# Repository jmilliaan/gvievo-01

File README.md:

# gvievo-01 — AGV / AMR platform

Control software for a 150 kg differential-drive vehicle. Two Oriental Motor
BLV-R drivers in CiA 402 Profile Velocity mode share one `can0` with a SICK MLS
magnetic line sensor (track reading and IMU); a SICK nanoScan3 safety scanner,
a Chafon RFID reader and a Modbus I/O island sit on Ethernet. The vehicle runs
as one systemd unit, `amr.service`: a supervisor, the hardware nodes, a web UI
on port 5001, and one *mode layer* at a time.

> ### gvievo-ce branch (2026-11-23)
> This branch is gvievo-main adapted to the **kyb unit** (host `gvipc-ce`, previously on
> `kyb-trackless`). It is the **tape product, like gvievo-main** (`tracked: null`): MLSE line
> following, slam_toolbox/AMCL, tape localization in shadow (`live: false`) until this site is
> taught. No MQTT: station calling stays off. Hardware: DIO island on enp1s0
> (`192.168.1.40`), nanoScan3 on enp2s0 (host `192.168.3.1`), enp3s0 empty. No Manual Arm input:
> MANUAL is always armed unless an emergency (E-stop OK = DI08 from Q3). Outputs DO0 movement horn,
> DO1 alarm horn only. See `documentation/electrical/01-schematic/io-mapping.md` section 4.

> ### Status (2026-09-21)
> **Two products on one stack.** The vehicle is a magnetic-tape AGV (the
> `LINE` mode: `amr_line`, ported from the tape controller that drove it
> before) with the SLAM AMR (`MAPPING`/`NAVIGATION`: slam_toolbox, AMCL, Nav2)
> as the upgrade. Which one a vehicle is comes from its profile.
>
> **The legacy standalone controller is gone (U11).** `main.py`, `app/` and
> `canworker.py` were deleted on 2026-09-21 after the ported LINE mode was
> accepted on the vehicle; the last deployable revision is tagged
> `legacy-final`. Its offline run logs are archived under
> `manuals/obsolete/legacy-runs/`. Nothing else on the vehicle owns `can0`.
>
> **The nanoScan3 is owned by the ROS stack** (`sick_safetyscanners2`); its
> liveness is read from `/amr/localization_state`. The protective-field
> outputs reach the drives through the FX3 in hardware, and the software only
> *reads* them (`/output_paths`) to explain a stop.

| | |
|---|---|
| Runtime | `amr.service` → `deploy/amr-supervisor.sh` → ROS 2 Humble, `amr_ws/` |
| Bus | CANopen 125 kbps, 50 Hz feedback by TPDO, setpoint by RPDO |
| Nodes | 1 left driver, 2 right driver, 10 SICK MLS (track at 100 Hz + gyro) |
| Manual | pendant and web jog 0.314 m/s = 1000 motor r/min (gvievo-ce 2026-11-23; was 0.60), only under selector MANUAL |
| Auto | tracked NORMAL 0.50 m/s (trips: mission `cruise_mps` 0.40), HIGH 0.90 m/s (`auto_high_ratio` 1.79, 2850 r/min motor; agv-01 since 2026-11-17, agv-02 still 1.7 / 0.85) only inside an MLS marker zone or a HIGH area; trips also NORMAL+ 0.65 m/s (`auto_plus_ratio` 1.3) inside a NORMAL+ area (slower area wins where they overlap); trackless 0.60 m/s |
| Tests | `tests/run_all.py` (`EXPECTED_CHECKS` guards the count) + `pytest` per ROS package, no hardware |

---

## ⚠️ Safety model

**This software moves a 150 kg vehicle and has no authentication.** Anyone who
can reach port 5001 can drive it. Keep it on a trusted network.

**The panel owns every entry into motion.** Manual jog (browser or pendant)
works only while the selector rests in MANUAL and the supervisor has granted
the manual lease; every autonomous start — a route, a survey move, the tape
follower — needs the selector in AUTO *and* a fresh physical Start press. No
web page can start the vehicle.

**One exception, only with `station.enabled: true` (default false).** An order
accepted from the station PC over MQTT leaves HOME for ATT with no Start press:
once, in AUTO, through the same 2 s horn, with no trolley detected and the rear
field clear. Every other stop and every hold still waits for Start. The bridge
holds no lease and no command topic, and the link is plain MQTT with broker
passwords and an ACL. This is a subset of VDA5050 3.0.0, not compliant. See
`manuals/station-call-plan.md`.

**A manual direction is HELD, not latched.** The jog pad re-POSTs while a
button is down; the command mux drops a stream whose stamp is older than its
`valid_for_s` (0.2 s). A closed tab, a dropped Wi-Fi link and a released
button are indistinguishable to the vehicle, which is the point.

**Arming excites the motor; it does not free it.** CiA 402 "Operation enabled"
is a servo lock, not a free shaft. Only the drive's `FREE` input releases the
brake, and `FREE` is on the CAN write deny-list. A disarmed vehicle cannot be
pushed either.

**Nothing in this repo is in the safety path.** The chain is lidar/encoders →
FX3 → HWTO1/HWTO2 → STO, wired in hardware with EDM returned to the FX3. Nothing
read over CAN or Ethernet is rated, redundant or certified, and nothing here may
decide whether it is safe to move. What the software adds is *recovery*: after
a lidar stop it resumes by itself once the field is clear; after the E-stop
button it waits for Start.

---

## Running

```bash
sudo systemctl start amr.service          # the only AGV boot service
systemctl status amr.service --no-pager
journalctl -u amr.service -f
```

Everything operational — boot checks, mode swaps, surveys, routes, holds,
rollback — is in [amr_ws/RUNBOOK.md](amr_ws/RUNBOOK.md). Deployment files
(`amr.service`, `amr.env`, the launch wrappers, `install.sh`, `validate.sh`, the
CAN bridge unit and udev template, the unclean-death helpers, the watchdog drop-ins)
are under [amr_ws/deploy/](amr_ws/deploy/); the platform freeze (ROS snapshot
source, apt pins and holds, `freeze.sh`) is under
[amr_ws/deploy/platform/](amr_ws/deploy/platform/). RUNBOOK section 5 says what
each installs.

**Which vehicle** comes from `AGV_PROFILE`, naming a file in `profiles/`.
Unset means `agv-01`. A name with no matching file is fatal at boot.

Bench work with the service stopped:

```bash
python3 -m agv_core.drivers.canbus.verify_bus       # nodes 1, 2, 10 answer
python3 -m agv_core.drivers.canbus.verify_drivers   # BLV-R identity and state
python3 -m agv_core.drivers.canbus.read_mls stream --nmt   # the track reading
python3 -m agv_core.drivers.canbus.read_imu show
```

Every bench tool takes the CAN owner lock first and refuses, naming the owner,
while `amr.service` (or another tool) holds it.

### Dependencies

ROS 2 Humble with Nav2, slam_toolbox, robot_localization,
`sick_safetyscanners2`; `python-can`, `pymodbus`, `flask`. The vehicle image
has them; nothing is pinned in `pyproject.toml` so the offline suite runs on a
dev box without them.

---

## Layout

**`agv_core/` is the library, `amr_ws/` is the runtime.** The runtime imports
the library; the library imports neither ROS nor Flask.

```
agv_core/          The vehicle library. No ROS, no Flask, no web tier.
  config.py          Loads and validates the profile. Everything imports this.
  kinematics.py      Wheel <-> body conversions from the profile geometry.
  ownerlock.py       The can/dio owner locks (fcntl); one owner per device.
  alarms.py, mission.py, paths.py, se2.py, fsio.py, fsutil.py, disk.py,
  panel.py, canmon.py, events.py, blindrun.py, lidarframe.py
  drivers/           dio.py (Modbus I/O island), rfid.py (Chafon reader)
  drivers/canbus/    CANopen decoders, the write deny-list (guard.py), RPDO
                     setup, and the bench tools listed above.

amr_ws/            The ROS 2 workspace (colcon, symlink install).
  src/amr_base         drive_node (the can0 owner), panel_node, cmd_mux,
                       odometry, commissioning, the MLS track reader
  src/amr_bringup      the supervisor, launch files, deploy/ and env/
  src/amr_line         LINE mode: the tape engine (autopilot.py, branch.py are
                       the verbatim port), the follower node, its authority
  src/amr_mission      routes, the run FSM, survey moves, the executor
  src/amr_navigation   route compiler, validation, Nav2 parameters
  src/amr_localization SLAM/AMCL glue, readiness, the localisation monitor
  src/amr_maps         map bundles and revisions
  src/amr_web          the Flask UI on 5001 and its ROS adapter
  src/amr_station      station_bridge_node: MQTT to the station PC (station.enabled only)
  src/amr_sim          fake base/panel/IMU/trolley, synthetic scan and tape
  src/amr_interfaces   messages and services

tests/             offline checks for agv_core (count: EXPECTED_CHECKS). run_all.py runs them.
profiles/          One JSON per vehicle. Every tunable parameter lives here.
manuals/           Device documentation, current plans and runbooks; obsolete/ = history
                   (vehicle reports, the SLAM plan, finished or superseded plans).
pyproject.toml     Packages agv_core; also the shared ruff and pytest config.
```

**`agv_core` is a real package, imported by package path.** `from agv_core
import config`, `from agv_core.drivers.canbus import guard`. ROS nodes run out
of the colcon install space, which is outside the repo, so
`env/vehicle.sh` (sourced by the service's `amr-supervisor.sh`) and `env/sim.sh`
put the repo root on `PYTHONPATH`; `amr_ws/deploy/validate.sh` refuses to install
if `agv_core/` is not where they expect it.

**Dependency graph:** `agv_core.config` imports only the standard library;
everything else imports it. No cycles. Nothing in `agv_core/drivers/canbus/`
imports `config` — those modules stay runnable on a bench. `tests/test_layout.py`
pins the package boundary.

---

## How it works

### One owner per device

`amr_base.drive_node` is the only process that opens `can0`, `panel_node` the
only one that writes the I/O island; each takes its owner lock at start. Inside
`drive_node`, one bus thread does every CAN transaction: feedback arrives by
TPDO at 50 Hz, the setpoint leaves by RPDO, and the MLS track reading rides on
TPDO1 `0x18A` at 100 Hz. Everything above it — mux, executor, follower — sends
stamped commands on topics and holds a *permit*; nothing else touches the bus.

### Authority

The supervisor grants one **lease** at a time (manual, autonomous, commissioning
or line), the command mux applies only the source that lease allows, and the
physical panel gates every transition: MANUAL for jog, AUTO plus a Start edge
for anything autonomous, Reset to end a run. A lease is bound to a
*generation* that rotates on every mode swap, so a replaced layer's commands
can never look fresh to the new mux.

### What the vehicle may write over CAN

[agv_core/drivers/canbus/guard.py](agv_core/drivers/canbus/guard.py) enforces a
deny-list on every write path of the bus owner (`amr_base.canopen`):

| | |
|---|---|
| **permitted** | `6040h` controlword, `6060h` modes, `6083h`/`6084h` ramps, `60FFh` target velocity, `607Ah`/`6081h` for PP, `1017h` heartbeat, PDO communication parameters |
| **refused** | `403Eh` (bit 6 is **FREE** — releases the holding brake on *both* drive wheels), `40D0h` clear ETO, `40C0h` alarm reset, `6040h` bit 7 fault reset, `1010h`/`1011h` store/restore, all `4xxxh` parameters, the PP safety objects |

A denied write raises rather than being silently dropped. RPDO mappings are
admitted only if the mapped object is itself writable — a mapping is a write
path by another name. Clearing ETO or resetting an alarm automatically would
be an automatic restart, which ISO 3691-4 prohibits: a latched drive alarm is
cleared by a power cycle, not by software.

### The MLS

The line sensor serves both products: its **track reading** (LCP positions,
`#LCP`, marker) feeds the tape follower, and its **gyro** carries the heading
for SLAM (the EKF weights it far above the wheels). Tape to the vehicle's left
reads *positive* millimetres. The reader starts the node by NMT so TPDO1 flows
and falls back to SDO polling (monitor only, ~10 Hz) if it does not; the
follower refuses to run on SDO samples or below `line_min_track_hz`.

---

## Configuration

Everything tunable lives in `profiles/<name>.json`, selected by `AGV_PROFILE`.
**`agv_core/config.py`'s docstring is the manual.**

1. **Unknown and missing keys are both fatal.**
2. **Only primitives are stored.** Anything derivable is derived.
3. **Validation runs before anything is published.**
4. **`profile_name` must match the filename.**

Speeds, ramps, the jog and pendant limits, the PP lock and the tape engine's
gains (`autopilot`) are all there — and the product: top-level
`"tracked": false` is the SLAM AMR, `true` the tape AGV that boots into LINE
and refuses maps and routes, `null` both: boots into LINE, surveys and the AMCL
position on the Mapping page (RUNBOOK §1, §2). The web UI's Params page shows every
value the running nodes actually use beside the profile's.

---

## Testing

```bash
python3 tests/run_all.py                                   # no hardware
cd amr_ws && source install/setup.bash && source env/vehicle.sh
env AMR_SIM_TESTS=0 ROS_DOMAIN_ID=89 python3 -m pytest -q src/*/test   # per package
ruff check agv_core tests && (cd amr_ws && ruff check src)
```

`run_all.py` **pins both the module list and the total check count**; a module
that stops being imported fails the run instead of silently costing coverage.
Raise `EXPECTED_CHECKS` deliberately, with a note, when adding checks; never
lower it to get a green run.

Simulation launch tests are opt-in (`AMR_SIM_TESTS=1`) and check mechanisms,
not tolerances. Vehicle acceptance is a witnessed session from a
`VEHICLE-TEST-*.txt` file at the repo root; reports go to
`manuals/obsolete/vehicle-reports/`.

---

## Invariants

**`agv_core` may not import ROS or Flask.** The bench tools and the nodes both
import it. `tests/test_layout.py` scans for it, lazy imports included, and
also refuses a bare sibling import inside the package.

**`agv_core/drivers/canbus/` is a runtime dependency, not a scratch directory.**
`amr_base.canopen` imports from it. Do **not** make those modules import
`config`; where they need a vehicle-specific value, take it as a parameter
defaulting to the module constant.

**NMT is per node.** The drive link puts *the drives* in Pre-operational for
PDO setup and starts *the drives*; it never broadcasts. A broadcast silenced
the MLS on the vehicle (2026-09-21).

**Wheel sign convention:** both drivers take a **positive** `60FFh` to travel
forward. If you swap a motor, re-flash a driver or remount a wheel, re-verify
on blocks and set `vehicle.invert_left` / `invert_right`.

**`autopilot.py` and `branch.py` are the port.** They are the engine that drove
this vehicle on tape and are not edited; if the gains look wrong, the gains
move in the profile.

---

## Known gaps

- **Tracked jobs are sim-tested only** (2026-10-08): the mission is the site's RFID
  tag table (`missions/line-a.json`, schema in `agv_core/mission.py`) - Home, an
  always-stop, destination stops (MRU1-4) and a track-end U-turn; speed comes from the MLS
  marker pairs (`high_zone`), not RFID (2026-10-09).
  The job (mission + destination) is set on Run; the vehicle may start anywhere
  on the line, then the physical Start runs it. Tag ids `0010`... are assumed to be what the RFID
  panel shows; stop positions, the 2 s speed change, the tape-end overshoot and the
  pivot reacquisition angle are settled on the floor.
- **No floor run of the tape follower yet** (LINE acceptance section 4).
- **0.90 m/s (tracked HIGH, agv-01; 0.85 before 2026-11-17) runs with no software gate,
  unvalidated** (operator decision 2026-10-08, manuals/tracked-speed-plan-1-no-slam.md D2;
  raised to 2850 r/min by the owner 2026-11-17): the nanoScan3 field set
  (`lidar.zones_validated` false) and the STO stopping distance from 0.90 m/s
  are a floor check before the first HIGH run. There is no FX3 encoder speed monitoring
  yet. HIGH needs a mission `high_zone` (MLS outer/inner marker codes); `line-a` carries one
  (codes 2/1), so HIGH runs wherever those marker pairs are laid.
- **`6064h` scaling is unverified** beyond the commissioning runs.
- **Backlash is unmeasured.** The encoders are motor-side of a 30:1 gearhead.
- **RFID reader is still on the US region (902.75–927.25 MHz)** and every read so far reports channel 0;
  Indonesia permits 920–923 MHz. Protocol is captured and CRC-verified (2026-10-08). The 0x0050
  heartbeat ships off (`rfid.heartbeat_s` 0) until a bench run shows it does not disturb streaming.
- MEXE02 load inertia is still `0: Small (2×)`; should be `1: Medium (7.5×)`.

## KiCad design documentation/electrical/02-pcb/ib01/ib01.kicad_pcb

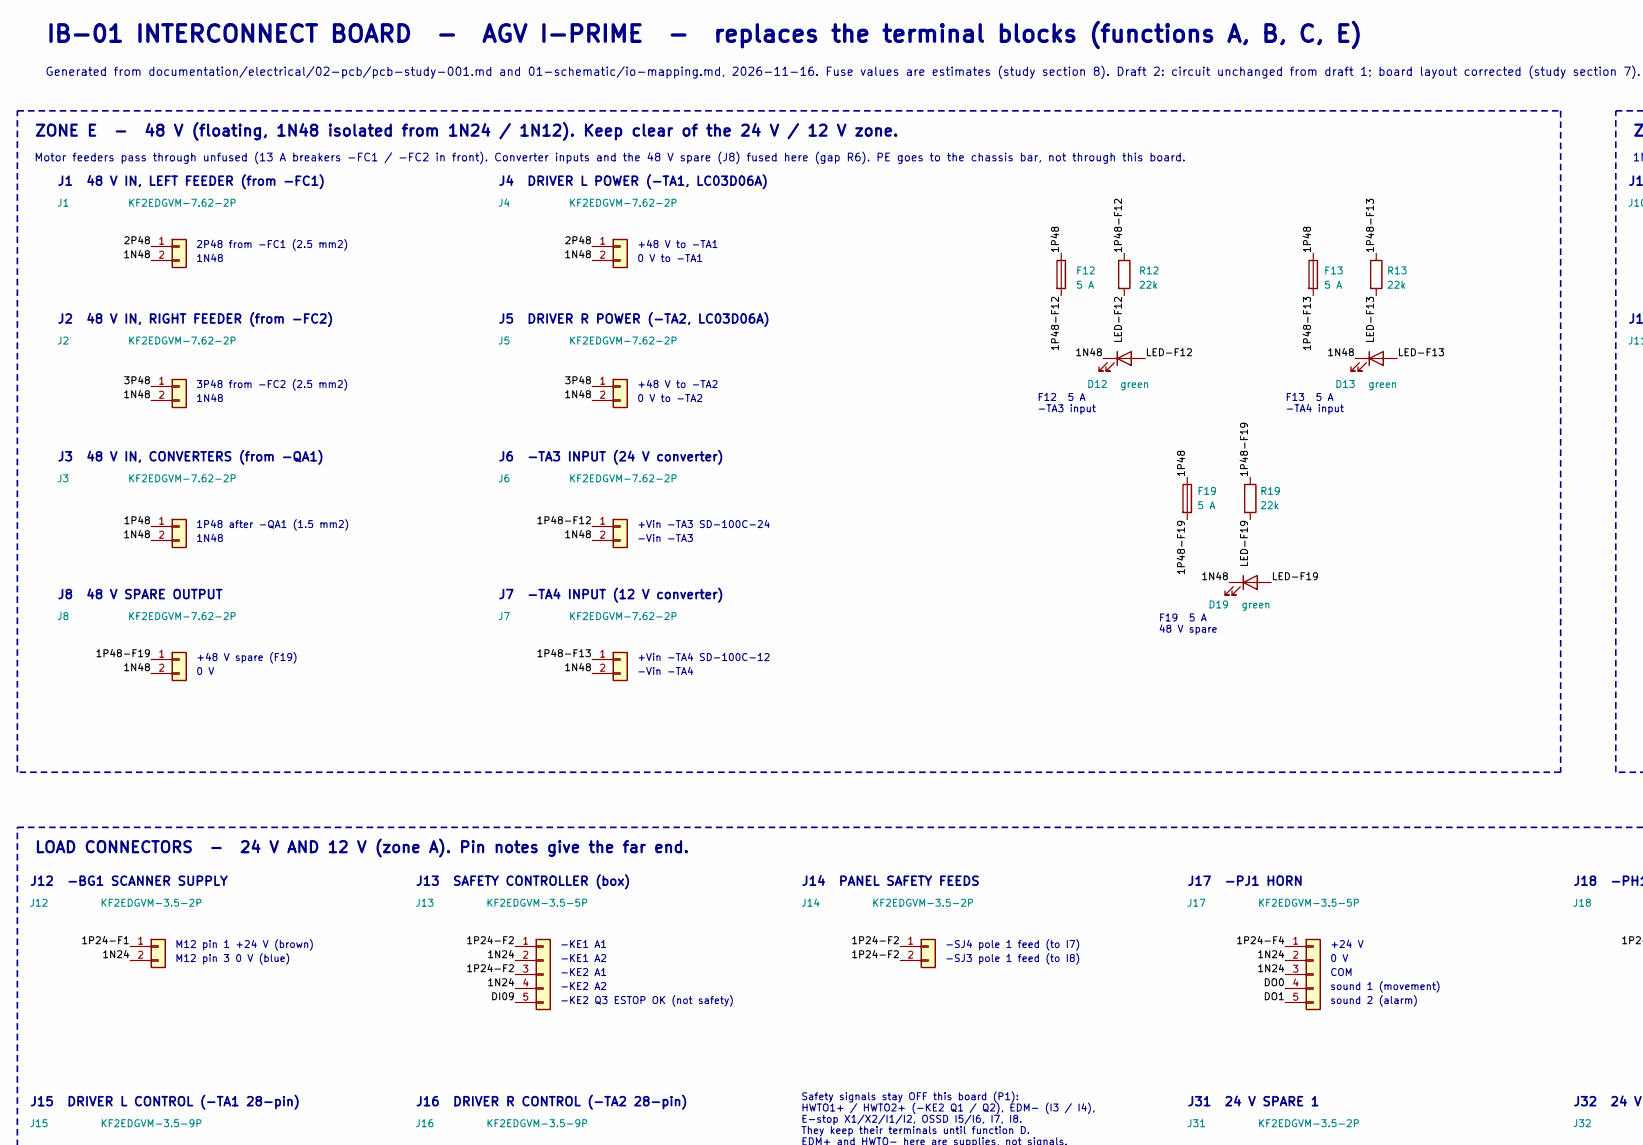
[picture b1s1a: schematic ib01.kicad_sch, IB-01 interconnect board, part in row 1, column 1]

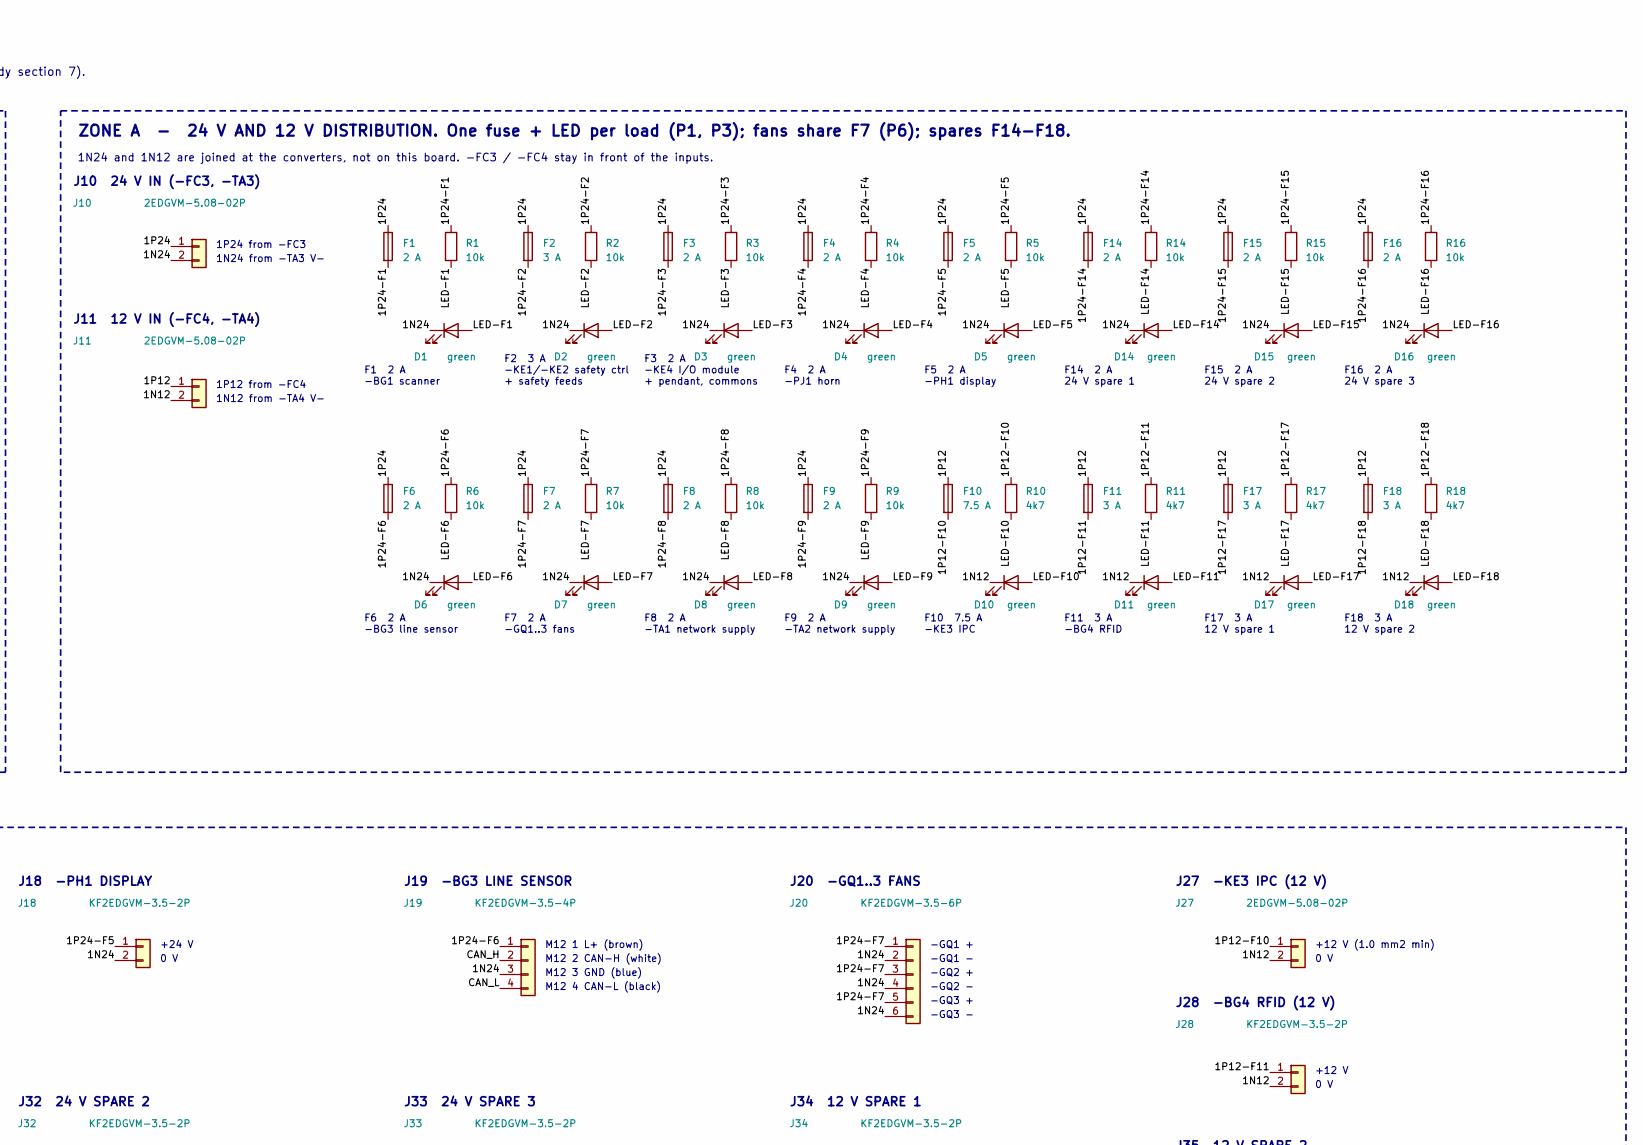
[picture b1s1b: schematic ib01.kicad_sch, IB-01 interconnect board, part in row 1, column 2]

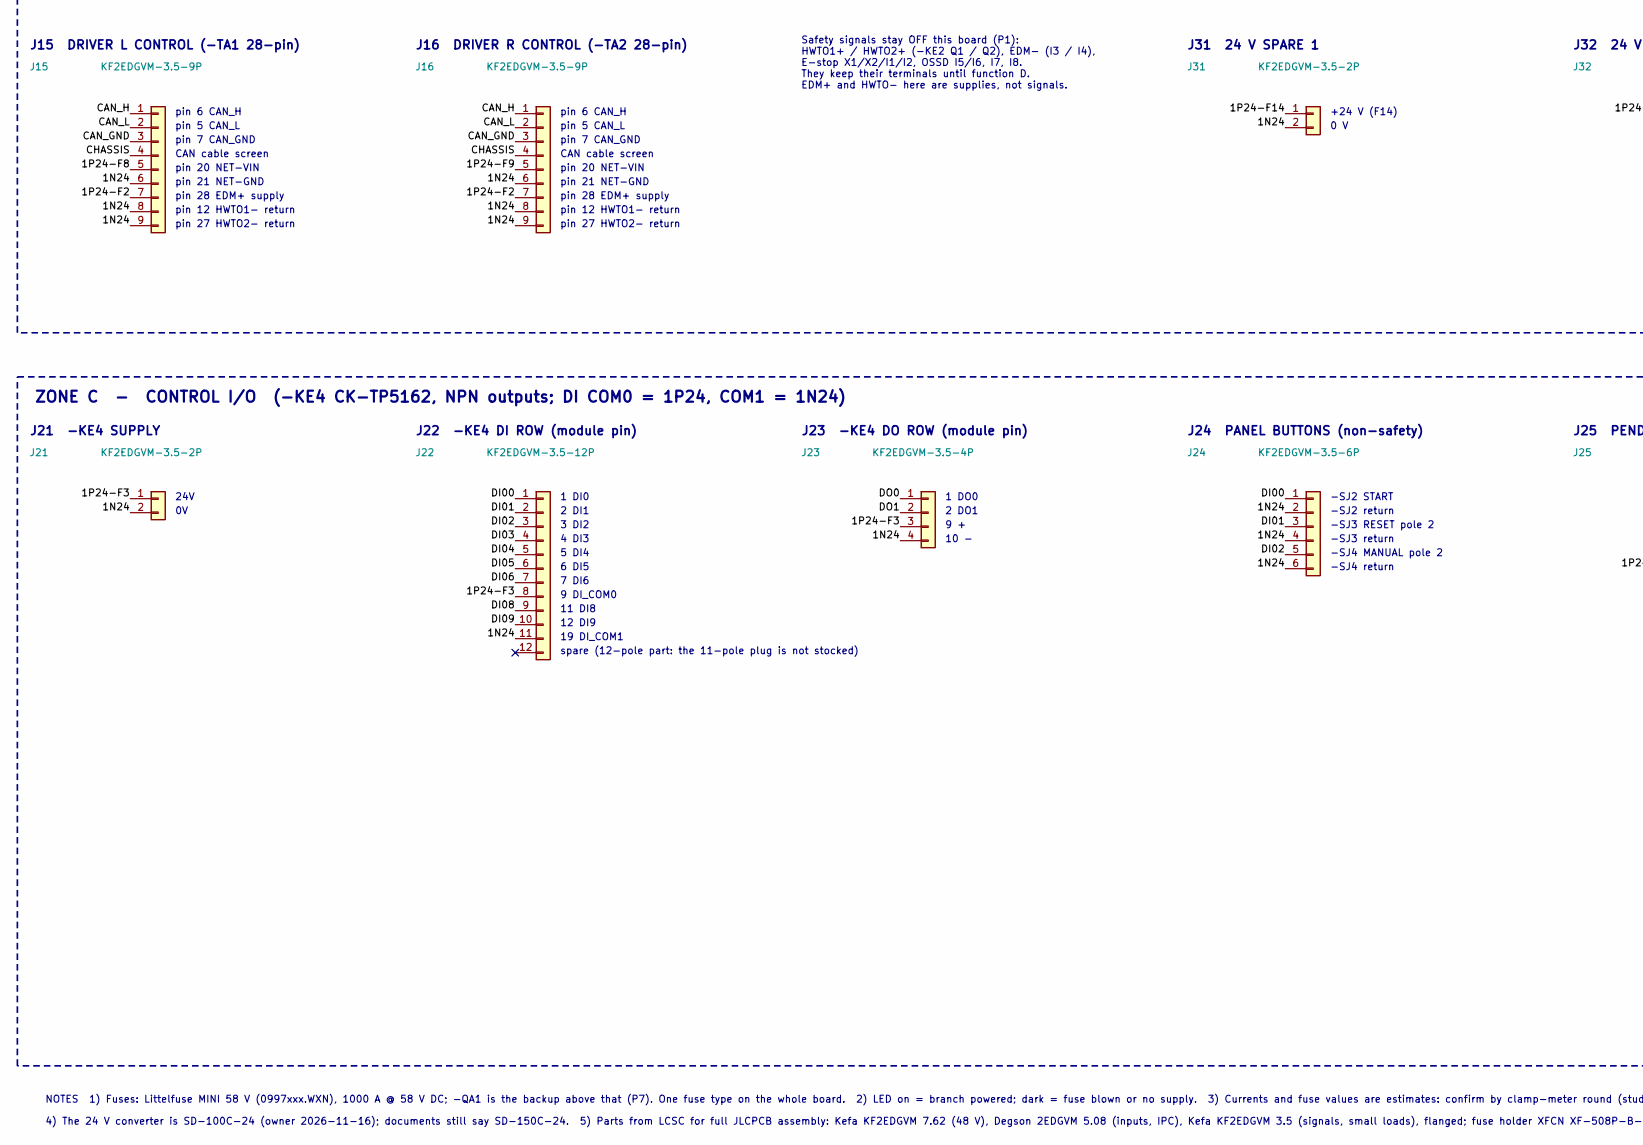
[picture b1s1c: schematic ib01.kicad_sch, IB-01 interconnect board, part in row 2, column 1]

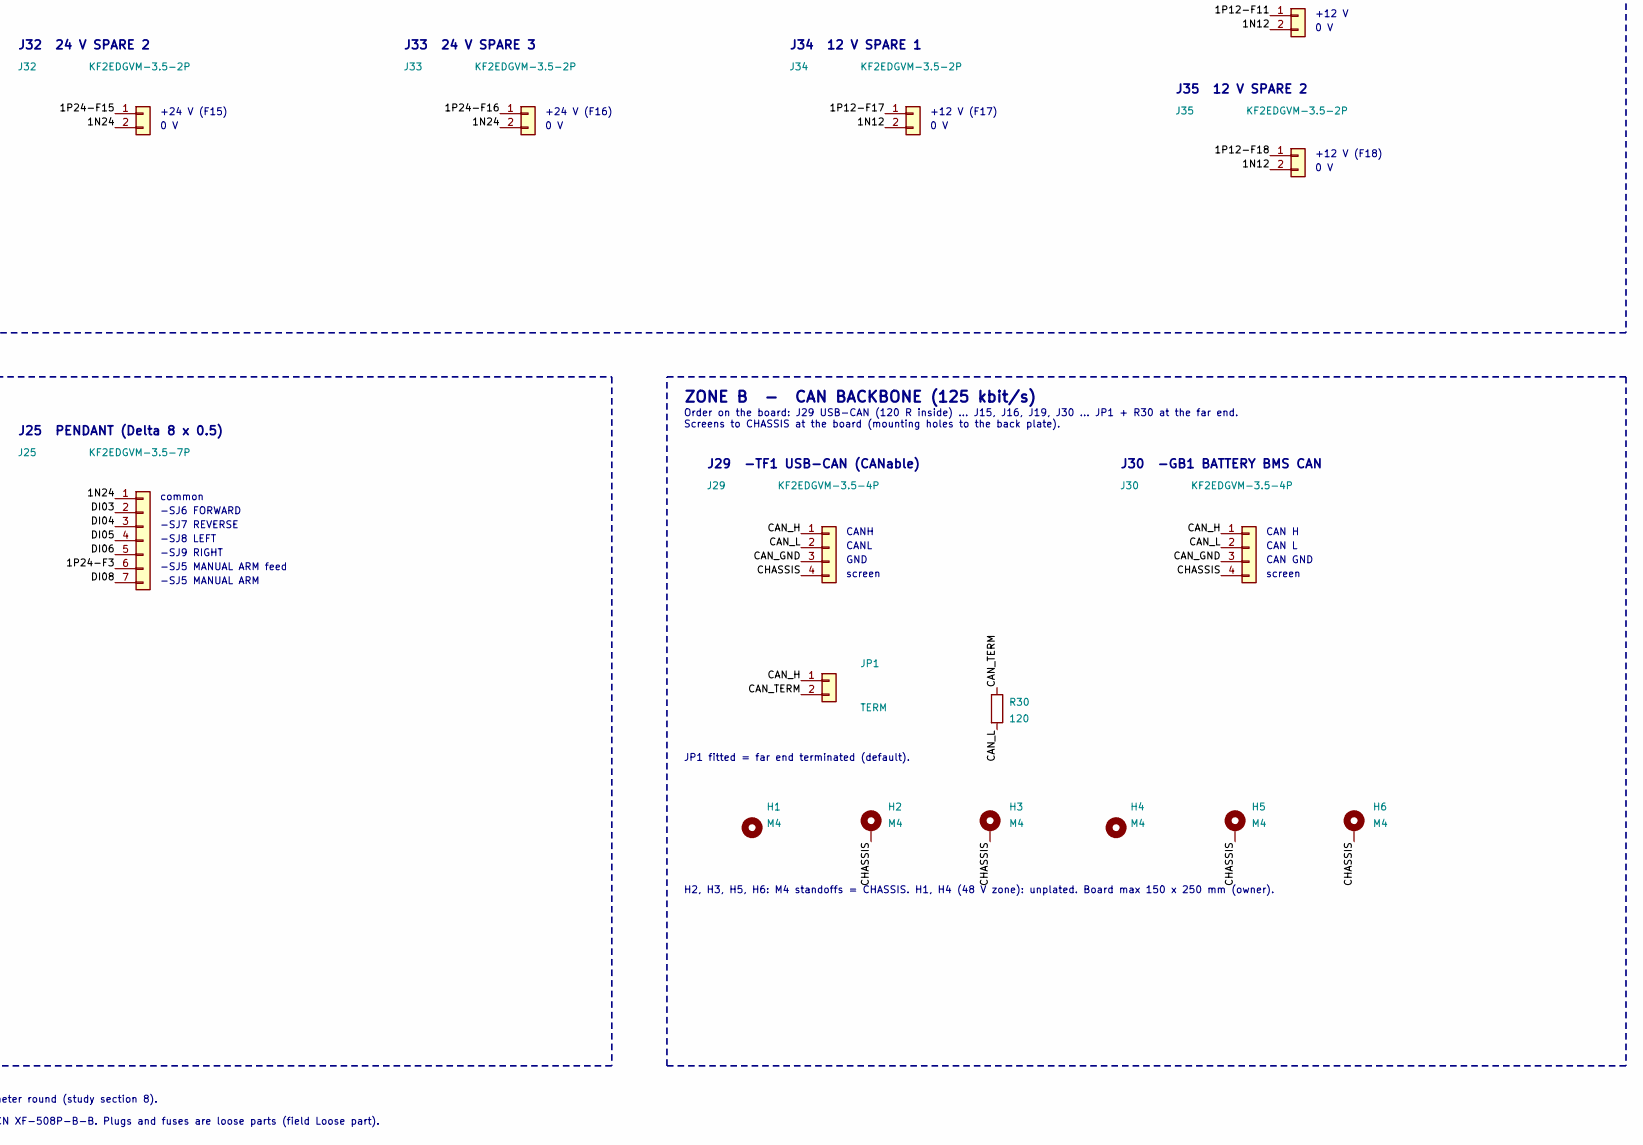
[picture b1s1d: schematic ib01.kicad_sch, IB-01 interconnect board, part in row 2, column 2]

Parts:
D1, D2, D3, D4, D5, D6, D7, D8, D9, D10, D11, D12, D13, D14, D15, D16, D17, D18, D19: green; LED_0805_2012Metric; LCSC C2297
F1, F3, F4, F5, F6, F7, F8, F9, F14, F15, F16: 2 A; XF-508P-B-B; MPN XFCN XF-508P-B-B MINI fuse holder, 500 V; LCSC C19727305
F2, F11, F17, F18: 3 A; XF-508P-B-B; MPN XFCN XF-508P-B-B MINI fuse holder, 500 V; LCSC C19727305
F10: 7.5 A; XF-508P-B-B; MPN XFCN XF-508P-B-B MINI fuse holder, 500 V; LCSC C19727305
F12, F13, F19: 5 A; XF-508P-B-B; MPN XFCN XF-508P-B-B MINI fuse holder, 500 V; LCSC C19727305
H1, H4: M4; MountingHole_4.3mm_M4
H2, H3, H5, H6: M4; MountingHole_4.3mm_M4_Pad_Via
J1, J2, J3, J4, J5, J6, J7, J8: KF2EDGVM-7.62-2P; MPN Kefa KF2EDGVM-7.62-2P (15 A / 630 V IEC); LCSC C441450
J10, J11, J27: 2EDGVM-5.08-02P; MPN Degson 2EDGVM-5.08-02P-14-100A(H) (20 A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; LCSC C699489
J12, J14, J18, J21, J28, J31, J32, J33, J34, J35: KF2EDGVM-3.5-2P; MPN Kefa KF2EDGVM-3.5-2P (8 A UL / 7 A IEC); LCSC C441407
J13, J17: KF2EDGVM-3.5-5P; MPN Kefa KF2EDGVM-3.5-5P (8 A UL / 7 A IEC); LCSC C441410
J15, J16: KF2EDGVM-3.5-9P; MPN Kefa KF2EDGVM-3.5-9P (8 A UL / 7 A IEC); LCSC C441414
J19, J23, J29, J30: KF2EDGVM-3.5-4P; MPN Kefa KF2EDGVM-3.5-4P (8 A UL / 7 A IEC); LCSC C441409
J20, J24: KF2EDGVM-3.5-6P; MPN Kefa KF2EDGVM-3.5-6P (8 A UL / 7 A IEC); LCSC C441411
J22: KF2EDGVM-3.5-12P; MPN Kefa KF2EDGVM-3.5-12P (8 A UL / 7 A IEC); LCSC C441405
J25: KF2EDGVM-3.5-7P; MPN Kefa KF2EDGVM-3.5-7P (8 A UL / 7 A IEC); LCSC C441412
JP1: TERM; PinHeader_1x02_P2.54mm_Vertical; MPN 2.54 mm 1x2 header; LCSC C32713268
R1, R2, R3, R4, R5, R6, R7, R8, R9, R14, R15, R16: 10k; R_0805_2012Metric; LCSC C17414
R10, R11, R17, R18: 4k7; R_0805_2012Metric; LCSC C17673
R12, R13, R19: 22k; R_1206_3216Metric; LCSC C25830
R30: 120; R_1206_3216Metric; LCSC C17909

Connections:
/1N12: D10.1 (K), D11.1 (K), D17.1 (K), D18.1 (K), J11.2, J27.2, J28.2, J34.2, J35.2
/1N24: D1.1 (K), D2.1 (K), D3.1 (K), D4.1 (K), D5.1 (K), D6.1 (K), D7.1 (K), D8.1 (K), D9.1 (K), D14.1 (K), D15.1 (K), D16.1 (K), J10.2, J12.2, J13.2, J13.4, J15.6, J15.8, J15.9, J16.6, J16.8, J16.9, J17.2, J17.3, J18.2, J19.3, J20.2, J20.4, J20.6, J21.2, J22.11, J23.4, J24.2, J24.4, J24.6, J25.1, J31.2, J32.2, J33.2
/1N48: D12.1 (K), D13.1 (K), D19.1 (K), J1.2, J2.2, J3.2, J4.2, J5.2, J6.2, J7.2, J8.2
/1P12: F10.1, F11.1, F17.1, F18.1, J11.1
/1P12-F10: F10.2, J27.1, R10.1
/1P12-F11: F11.2, J28.1, R11.1
/1P12-F17: F17.2, J34.1, R17.1
/1P12-F18: F18.2, J35.1, R18.1
/1P24: F1.1, F2.1, F3.1, F4.1, F5.1, F6.1, F7.1, F8.1, F9.1, F14.1, F15.1, F16.1, J10.1
/1P24-F1: F1.2, J12.1, R1.1
/1P24-F2: F2.2, J13.1, J13.3, J14.1, J14.2, J15.7, J16.7, R2.1
/1P24-F3: F3.2, J21.1, J22.8, J23.3, J25.6, R3.1
/1P24-F4: F4.2, J17.1, R4.1
/1P24-F5: F5.2, J18.1, R5.1
/1P24-F6: F6.2, J19.1, R6.1
/1P24-F7: F7.2, J20.1, J20.3, J20.5, R7.1
/1P24-F8: F8.2, J15.5, R8.1
/1P24-F9: F9.2, J16.5, R9.1
/1P24-F14: F14.2, J31.1, R14.1
/1P24-F15: F15.2, J32.1, R15.1
/1P24-F16: F16.2, J33.1, R16.1
/1P48: F12.1, F13.1, F19.1, J3.1
/1P48-F12: F12.2, J6.1, R12.1
/1P48-F13: F13.2, J7.1, R13.1
/1P48-F19: F19.2, J8.1, R19.1
/2P48: J1.1, J4.1
/3P48: J2.1, J5.1
/CAN_GND: J15.3, J16.3, J29.3, J30.3
/CAN_H: J15.1, J16.1, J19.2, J29.1, J30.1, JP1.1
/CAN_L: J15.2, J16.2, J19.4, J29.2, J30.2, R30.2
/CAN_TERM: JP1.2, R30.1
/CHASSIS: H2.1, H3.1, H5.1, H6.1, J15.4, J16.4, J29.4, J30.4
/DI00: J22.1, J24.1
/DI01: J22.2, J24.3
/DI02: J22.3, J24.5
/DI03: J22.4, J25.2
/DI04: J22.5, J25.3
/DI05: J22.6, J25.4
/DI06: J22.7, J25.5
/DI08: J22.9, J25.7
/DI09: J13.5, J22.10
/DO0: J17.4, J23.1
/DO1: J17.5, J23.2
/LED-F1: D1.2 (A), R1.2
/LED-F2: D2.2 (A), R2.2
/LED-F3: D3.2 (A), R3.2
/LED-F4: D4.2 (A), R4.2
/LED-F5: D5.2 (A), R5.2
/LED-F6: D6.2 (A), R6.2
/LED-F7: D7.2 (A), R7.2
/LED-F8: D8.2 (A), R8.2
/LED-F9: D9.2 (A), R9.2
/LED-F10: D10.2 (A), R10.2
/LED-F11: D11.2 (A), R11.2
/LED-F12: D12.2 (A), R12.2
/LED-F13: D13.2 (A), R13.2
/LED-F14: D14.2 (A), R14.2
/LED-F15: D15.2 (A), R15.2
/LED-F16: D16.2 (A), R16.2
/LED-F17: D17.2 (A), R17.2
/LED-F18: D18.2 (A), R18.2
/LED-F19: D19.2 (A), R19.2

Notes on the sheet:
IB-01 INTERCONNECT BOARD - AGV I-PRIME - replaces the terminal blocks (functions A, B, C, E)
Generated from documentation/electrical/02-pcb/pcb-study-001.md and 01-schematic/io-mapping.md, 2026-11-16. Fuse values are estimates (study section 8). Draft 2: circuit unchanged from draft 1; board layout corrected (study section 7).
ZONE E - 48 V (floating, 1N48 isolated from 1N24 / 1N12). Keep clear of the 24 V / 12 V zone.
Motor feeders pass through unfused (13 A breakers -FC1 / -FC2 in front). Converter inputs and the 48 V spare (J8) fused here (gap R6). PE goes to the chassis bar, not through this board.
J1 48 V IN, LEFT FEEDER (from -FC1)
2P48 from -FC1 (2.5 mm2)
1N48
J2 48 V IN, RIGHT FEEDER (from -FC2)
3P48 from -FC2 (2.5 mm2)
J3 48 V IN, CONVERTERS (from -QA1)
1P48 after -QA1 (1.5 mm2)
J4 DRIVER L POWER (-TA1, LC03D06A)
+48 V to -TA1
0 V to -TA1
J5 DRIVER R POWER (-TA2, LC03D06A)
+48 V to -TA2
0 V to -TA2
J6 -TA3 INPUT (24 V converter)
+Vin -TA3 SD-100C-24
-Vin -TA3
J7 -TA4 INPUT (12 V converter)
+Vin -TA4 SD-100C-12
-Vin -TA4
F12 5 A -TA3 input
F13 5 A -TA4 input
J8 48 V SPARE OUTPUT
+48 V spare (F19)
0 V
F19 5 A 48 V spare
ZONE A - 24 V AND 12 V DISTRIBUTION. One fuse + LED per load (P1, P3); fans share F7 (P6); spares F14-F18.
1N24 and 1N12 are joined at the converters, not on this board. -FC3 / -FC4 stay in front of the inputs.
J10 24 V IN (-FC3, -TA3)
1P24 from -FC3
1N24 from -TA3 V-
J11 12 V IN (-FC4, -TA4)
1P12 from -FC4
1N12 from -TA4 V-
F1 2 A -BG1 scanner
F2 3 A -KE1/-KE2 safety ctrl + safety feeds
F3 2 A -KE4 I/O module + pendant, commons

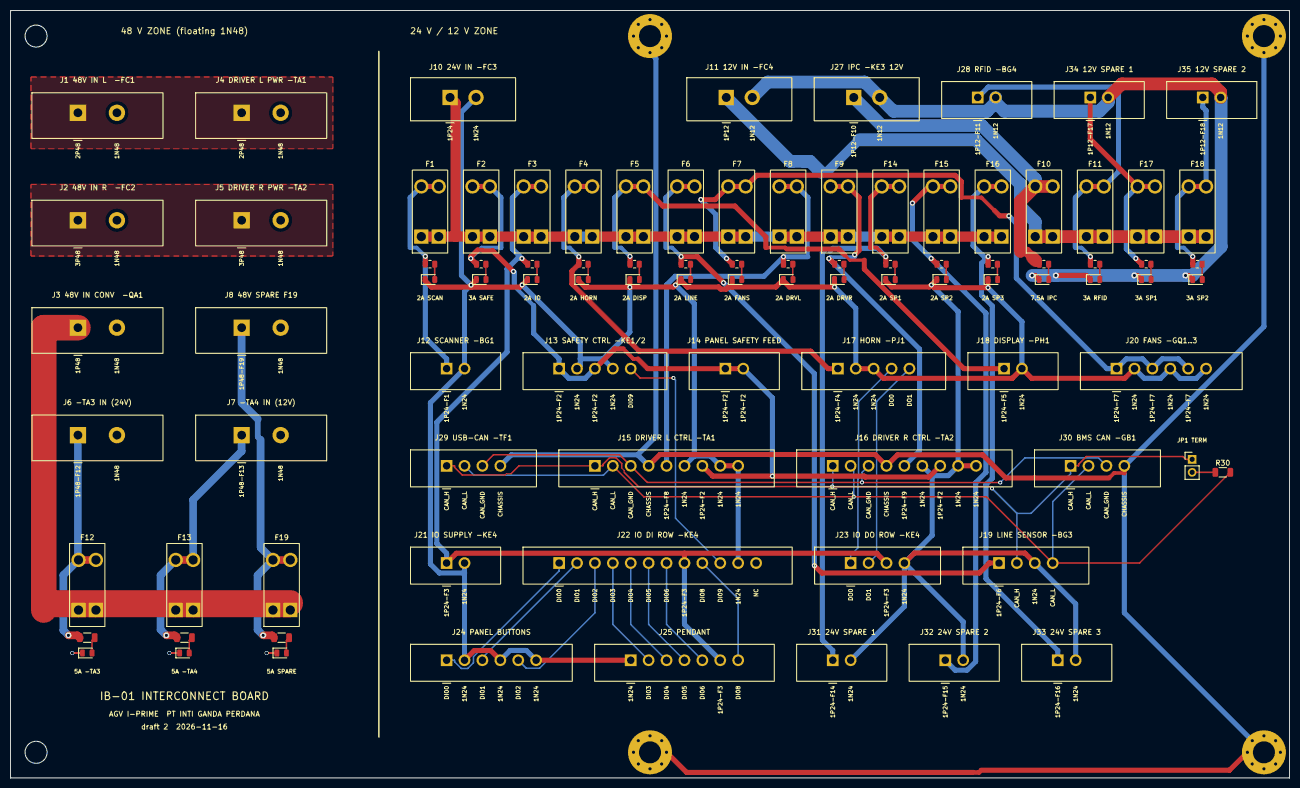
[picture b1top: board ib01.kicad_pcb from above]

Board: 2 copper layers, 250.0 x 150.0 mm, 98 parts (0 on the bottom side), 62 nets.

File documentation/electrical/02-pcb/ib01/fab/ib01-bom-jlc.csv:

Comment,Designator,Footprint,LCSC Part #
green,"D1,D2,D3,D4,D5,D6,D7,D8,D9,D10,D11,D12,D13,D14,D15,D16,D17,D18,D19",LED_0805_2012Metric,C2297
MINI fuse holder,"F1,F2,F3,F4,F5,F6,F7,F8,F9,F10,F11,F12,F13,F14,F15,F16,F17,F18,F19",XF-508P-B-B,C19727305
KF2EDGVM-7.62-2P,"J1,J2,J3,J4,J5,J6,J7,J8",KF2EDGVM-7.62-2P,C441450
2EDGVM-5.08-02P,"J10,J11,J27",2EDGVM-5.08-02P,C699489
KF2EDGVM-3.5-2P,"J12,J14,J18,J21,J28,J31,J32,J33,J34,J35",KF2EDGVM-3.5-2P,C441407
KF2EDGVM-3.5-5P,"J13,J17",KF2EDGVM-3.5-5P,C441410
KF2EDGVM-3.5-9P,"J15,J16",KF2EDGVM-3.5-9P,C441414
KF2EDGVM-3.5-4P,"J19,J23,J29,J30",KF2EDGVM-3.5-4P,C441409
KF2EDGVM-3.5-6P,"J20,J24",KF2EDGVM-3.5-6P,C441411
KF2EDGVM-3.5-12P,J22,KF2EDGVM-3.5-12P,C441405
KF2EDGVM-3.5-7P,J25,KF2EDGVM-3.5-7P,C441412
TERM,JP1,PinHeader_1x02_P2.54mm_Vertical,C32713268
10k,"R1,R2,R3,R4,R5,R6,R7,R8,R9,R14,R15,R16",R_0805_2012Metric,C17414
4k7,"R10,R11,R17,R18",R_0805_2012Metric,C17673
22k,"R12,R13,R19",R_1206_3216Metric,C25830
120,R30,R_1206_3216Metric,C17909
